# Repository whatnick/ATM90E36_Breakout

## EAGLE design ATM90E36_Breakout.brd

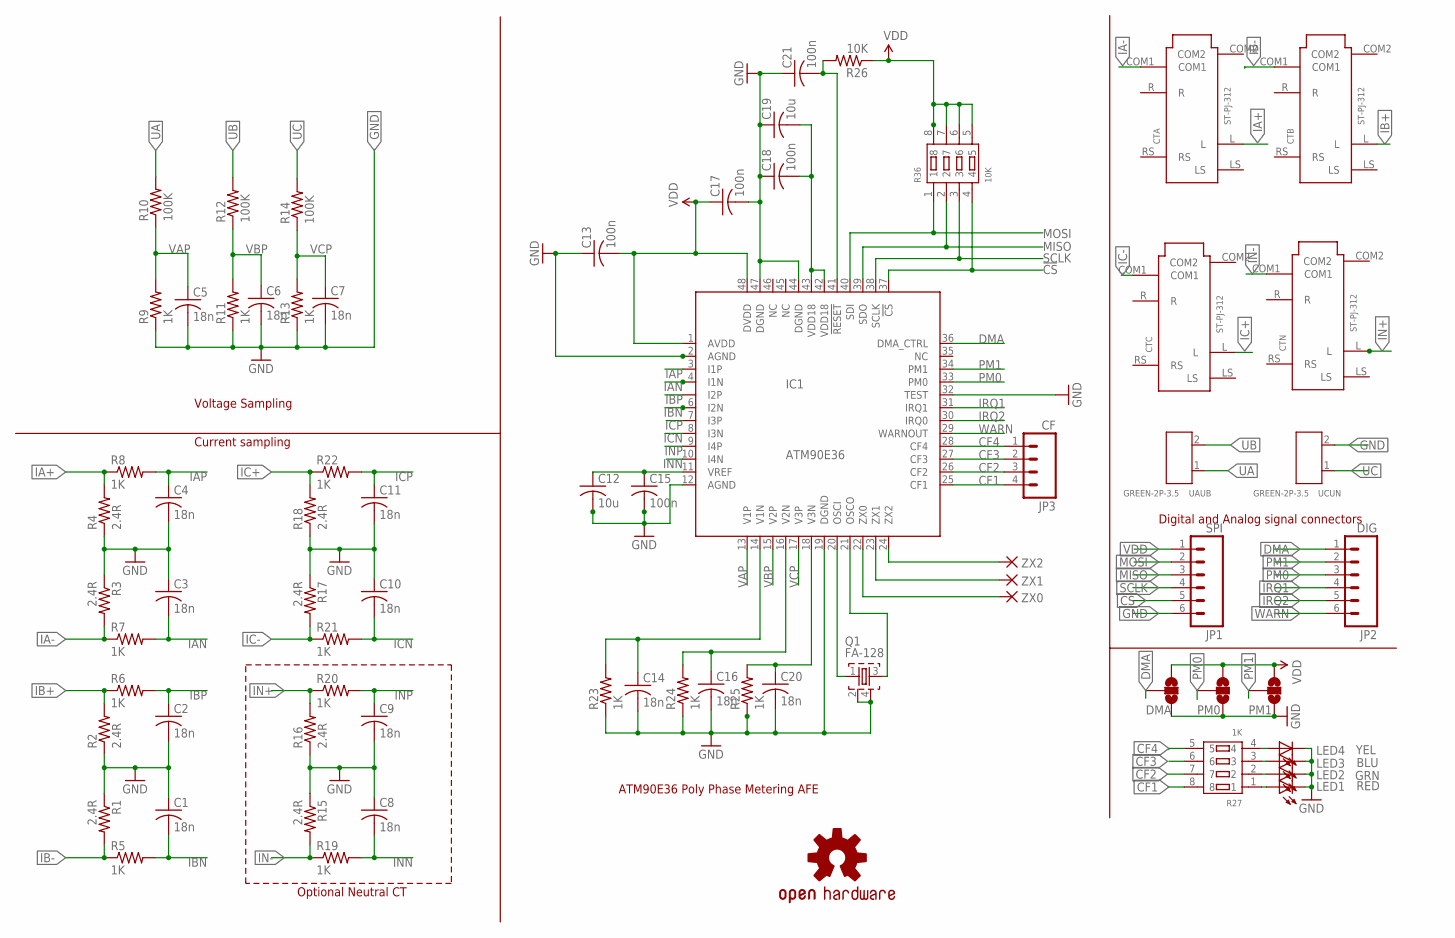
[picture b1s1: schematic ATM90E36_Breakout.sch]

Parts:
C1, C2, C3, C4, C5, C6, C7, C8, C9, C10, C11, C14, C16, C20: 18n; C0603
C12, C19: 10u; C0805
C13, C15, C17, C18, C21: 100n; C0603
CTA: ST-PJ-312; AUDIO6P-SMD-3.5-14.0X6.4X5.0MM
CTB: ST-PJ-312; AUDIO6P-SMD-3.5-14.0X6.4X5.0MM
CTC: ST-PJ-312; AUDIO6P-SMD-3.5-14.0X6.4X5.0MM
CTN: ST-PJ-312; AUDIO6P-SMD-3.5-14.0X6.4X5.0MM
DMA: JUMPER-PAD-3-NOFULL_BOX_SILK; PAD-JUMPER-3-NO_YES_SILK_FULL_BOX
IC1: ATM90E36; TQFP48
JP1: SPI; 1X06_LOCK
JP2: DIG; 1X06_LOCK
JP3: CF; 1X04_LOCK
LED1: RED; CHIP-LED0603
LED2: GRN; CHIP-LED0603
LED3: BLU; CHIP-LED0603
LED4: YEL; CHIP-LED0603
LOGO1: OSHW-LOGOM; OSHW-LOGO-M
PM0, PM1: JUMPER-PAD-3-NOFULL_BOX_SILK; PAD-JUMPER-3-NO_YES_SILK_FULL_BOX
Q1: FA-128
R1, R2, R3, R4, R15, R16, R17, R18: 2.4R; R0603
R5, R6, R7, R8, R9, R11, R13, R19, R20, R21, R22, R23, R24, R25: 1K; R0603
R10, R12, R14: 100K; R0603
R26: 10K; R0603
R27: 1K; RA1206-8
R36: 10K; RA1206-8
UAUB: GREEN-2P-3.5; H2-3.5-7.0X7.0MM
UCUN: GREEN-2P-3.5; H2-3.5-7.0X7.0MM
ZX0, ZX2: ZX0; SMD1,27-2,54
ZX1: ZX1; SMD1,27-2,54

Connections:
!CS: IC1.37 (!CS), JP1.5, R36.4
CF1: IC1.25 (CF1), JP3.4, R27.8
CF2: IC1.26 (CF2), JP3.3, R27.7
CF3: IC1.27 (CF3), JP3.2, R27.6
CF4: IC1.28 (CF4), JP3.1, R27.5
DMA: DMA.2, IC1.36 (DMA_CTRL), JP2.1
GND: C1.1, C2.2, C3.1, C4.2, C5.2, C6.2, C7.2, C8.1, C9.2, C10.1, C11.2, C12.2, C13.1, C14.2, C15.2, C16.2, C17.2, C18.1, C19.1, C20.2, C21.1, DMA.3, IC1.2 (AGND), IC1.12 (AGND), IC1.19 (DGND), IC1.32 (TEST), IC1.44 (DGND), IC1.47 (DGND), JP1.6, LED1.C, LED2.C, LED3.C, LED4.C, PM0.3, PM1.3, Q1.2, Q1.4, R1.1, R2.1, R3.1, R4.1, R9.1, R11.1, R13.1, R15.1, R16.1, R17.1, R18.1, R23.1, R24.1, R25.1, UCUN.2
IA+: CTA.L, R4.2, R8.1
IA-: CTA.COM1, R3.2, R7.1
IAN: C3.2, IC1.4 (I1N), R7.2
IAP: C4.1, IC1.3 (I1P), R8.2
IB+: CTB.L, R2.2, R6.1
IB-: CTB.COM1, R1.2, R5.1
IBN: C1.2, IC1.6 (I2N), R5.2
IBP: C2.1, IC1.5 (I2P), R6.2
IC+: CTC.L, R18.2, R22.1
IC-: CTC.COM1, R17.2, R21.1
ICN: C10.2, IC1.8 (I3N), R21.2
ICP: C11.1, IC1.7 (I3P), R22.2
IN+: CTN.L, R16.2, R20.1
IN-: CTN.COM1, R15.2, R19.1
INN: C8.2, IC1.10 (I4N), R19.2
INP: C9.1, IC1.9 (I4P), R20.2
IRQ1: IC1.31 (IRQ1), JP2.4
IRQ2: IC1.30 (IRQ0), JP2.5
MISO: IC1.39 (SDO), JP1.3, R36.2
MOSI: IC1.40 (SDI), JP1.2, R36.1
unnamed: C21.2, IC1.41 (!RESET), R26.2
unnamed: LED4.A, R27.4
unnamed: LED3.A, R27.3
unnamed: LED2.A, R27.2
unnamed: LED1.A, R27.1
unnamed: C14.1, IC1.14 (V1N), R23.2
unnamed: IC1.20 (OSCI), Q1.1
unnamed: C16.1, IC1.16 (V2N), R24.2
unnamed: C20.1, IC1.18 (V3N), R25.2
unnamed: IC1.21 (OSCO), Q1.3
unnamed: C18.2, C19.2, IC1.42 (VDD18), IC1.43 (VDD18)
unnamed: C12.1, C15.1, IC1.11 (VREF)
PM0: IC1.33 (PM0), JP2.3, PM0.2
PM1: IC1.34 (PM1), JP2.2, PM1.2
SCLK: IC1.38 (SCLK), JP1.4, R36.3
UA: R10.2, UAUB.1
UB: R12.2, UAUB.2
UC: R14.2, UCUN.1
VAP: C5.1, IC1.13 (V1P), R9.2, R10.1
VBP: C6.1, IC1.15 (V2P), R11.2, R12.1
VCP: C7.1, IC1.17 (V3P), R13.2, R14.1
VDD: C13.2, C17.1, DMA.1, IC1.1 (AVDD), IC1.48 (DVDD), JP1.1, PM0.1, PM1.1, R26.1, R36.5, R36.6, R36.7, R36.8
WARN: IC1.29 (WARNOUT), JP2.6
ZX0: IC1.22 (ZX0), ZX0.1
ZX1: IC1.23 (ZX1), ZX1.1
ZX2: IC1.24 (ZX2), ZX2.1

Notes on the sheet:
Current sampling
Optional Neutral CT
Voltage Sampling
ATM90E36 Poly Phase Metering AFE
Digital and Analog signal connectors

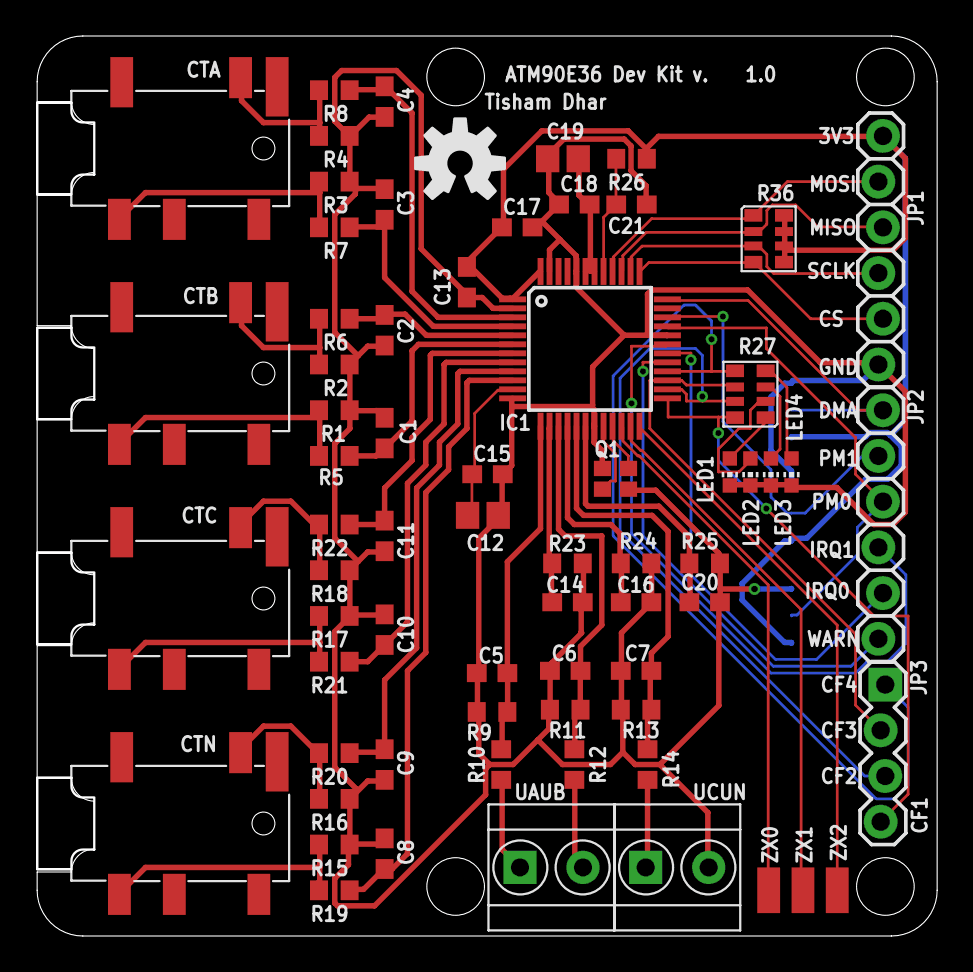
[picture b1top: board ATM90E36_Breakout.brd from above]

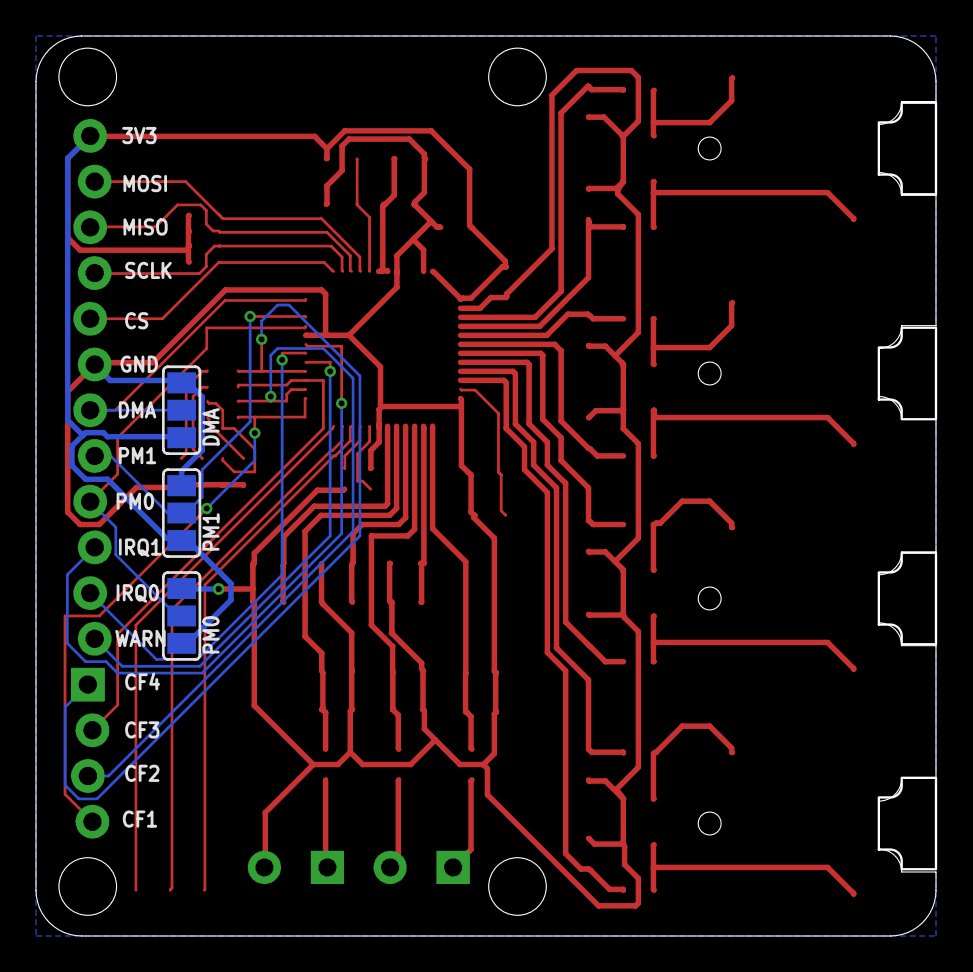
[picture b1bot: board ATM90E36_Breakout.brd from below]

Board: 2 copper layers, 50.0 x 50.0 mm, 71 parts (3 on the bottom side), 53 nets.

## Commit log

2016-12-27 Initial import of fully routed board
2016-12-28 Renamed CT's and improved cutouts
2016-12-28 Recreated milling with dimensions

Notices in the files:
parts and their libraries:
SparkFun-Aesthetics: Licensing: Creative Commons ShareAlike 4.0 International - https://creativecommons.org/licenses/by-sa/4.0
